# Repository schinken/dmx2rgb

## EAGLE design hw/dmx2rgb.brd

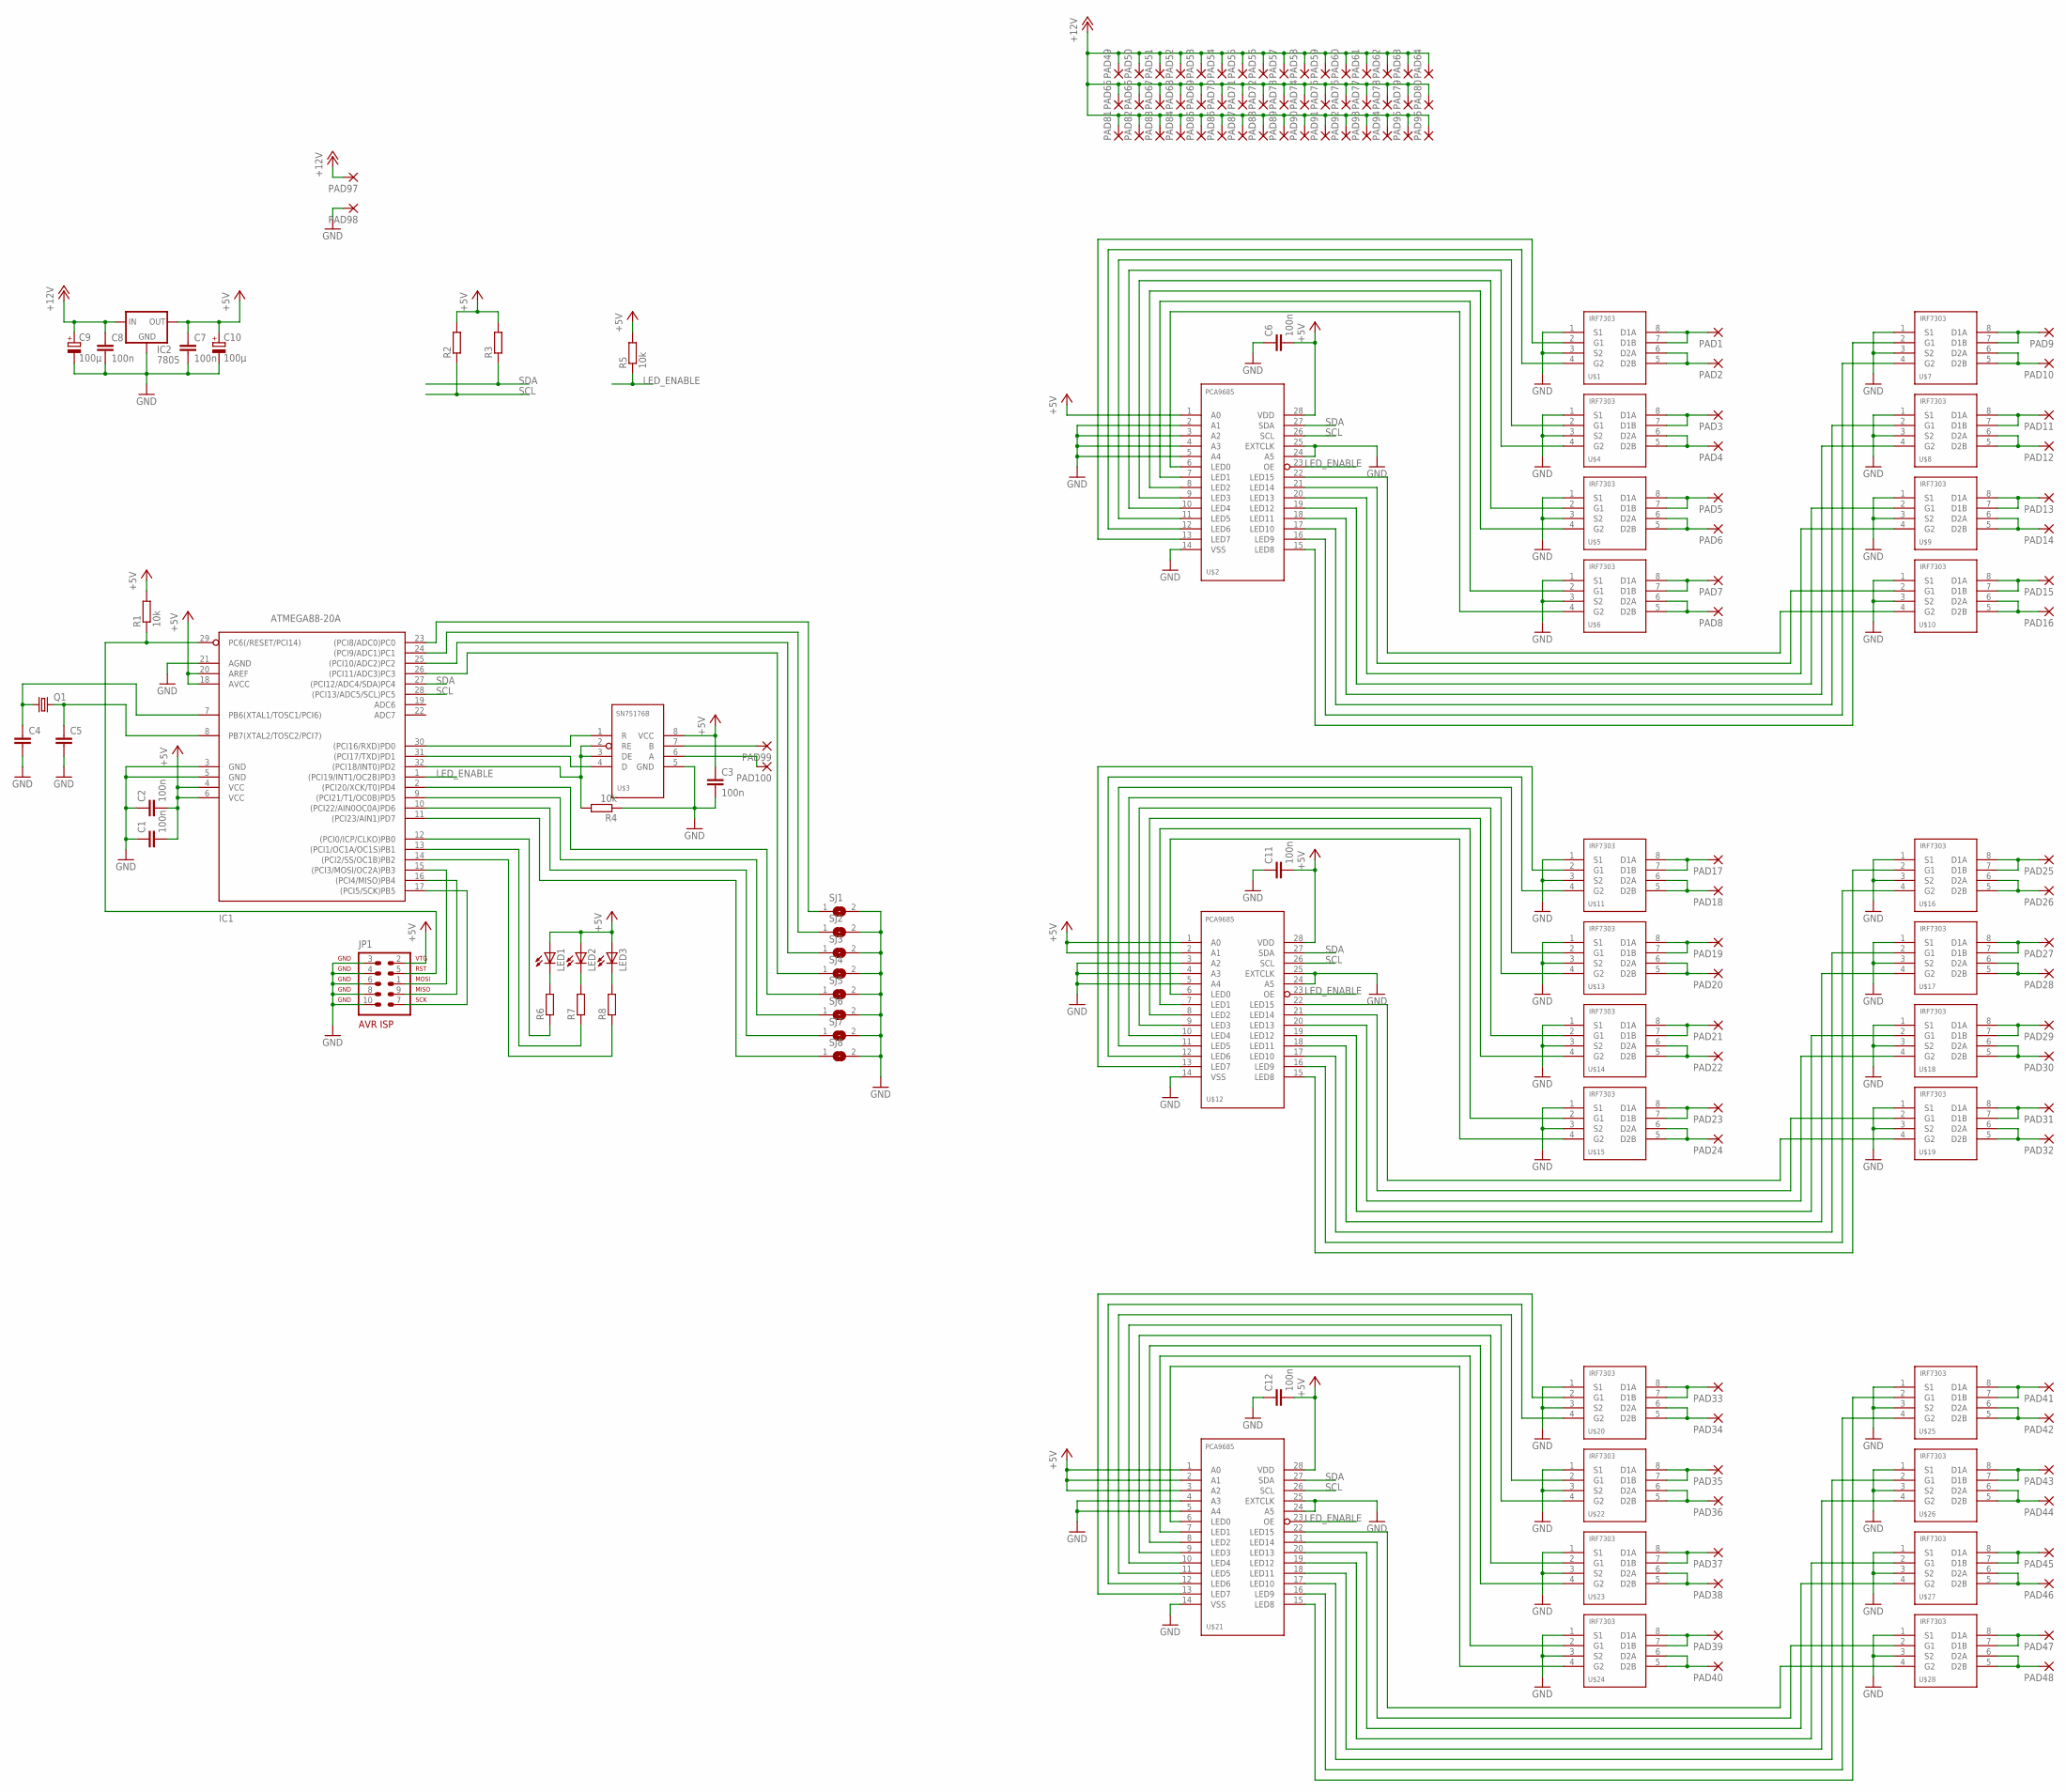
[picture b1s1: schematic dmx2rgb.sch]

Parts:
C1, C2, C3, C6, C7, C8, C11, C12: 100n; CHIP_0805
C4, C5: C0805; CHIP_0805
C9, C10: 100µ; E2,5-7
IC1: ATMEGA88-20A; TQFP32-08
IC2: 7805; 78LXX
JP1: AVR-ISP-10
LED1, LED2, LED3: LEDCHIPLED_0805; CHIPLED_0805
PAD1, PAD2, PAD3, PAD4, PAD5, PAD6, PAD7, PAD8, PAD9, PAD10, PAD11, PAD12, PAD13, PAD14, PAD15, PAD16, PAD17, PAD18, PAD19, PAD20, PAD21, PAD22, PAD23, PAD24, PAD25, PAD26, PAD27, PAD28, PAD29, PAD30, PAD31, PAD32, PAD33, PAD34, PAD35, PAD36, PAD37, PAD38, PAD39, PAD40, PAD41, PAD42, PAD43, PAD44, PAD45, PAD46, PAD47, PAD48, PAD49, PAD50, PAD51, PAD52, PAD53, PAD54, PAD55, PAD56, PAD57, PAD58, PAD59, PAD60, PAD61, PAD62, PAD63, PAD64, PAD65, PAD66, PAD67, PAD68, PAD69, PAD70, PAD71, PAD72, PAD73, PAD74, PAD75, PAD76, PAD77, PAD78, PAD79, PAD80, PAD81, PAD82, PAD83, PAD84, PAD85, PAD86, PAD87, PAD88, PAD89, PAD90, PAD91, PAD92, PAD93, PAD94, PAD95, PAD96, PAD99, PAD100: SMD_PAD_LONG
PAD97, PAD98: SMD5; SMD2,54-5,08
Q1: CRYSTAL49; HC49/S
R1, R4, R5: 10k; CHIP_0805
R2, R3, R6, R7, R8: R0805; CHIP_0805
SJ1, SJ2, SJ3, SJ4, SJ5, SJ6, SJ7, SJ8: SJ
U$1, U$4, U$5, U$6, U$7, U$8, U$9, U$10, U$11, U$13, U$14, U$15, U$16, U$17, U$18, U$19, U$20, U$22, U$23, U$24, U$25, U$26, U$27, U$28: IRF7303; SO8
U$2, U$12, U$21: PCA9685; TSSOP28
U$3: SN75176B; SO8

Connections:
+5V: C1.2, C2.2, C3.1, C6.2, C7.1, C10.+, C11.2, C12.2, IC1.4 (VCC), IC1.6 (VCC), IC1.18 (AVCC), IC1.20 (AREF), IC2.OUT, JP1.2, LED1.A, LED2.A, LED3.A, R1.2, R2.2, R3.2, R5.2, U$2.1 (A0), U$2.28 (VDD), U$3.8 (VCC), U$12.1 (A0), U$12.2 (A1), U$12.28 (VDD), U$21.1 (A0), U$21.2 (A1), U$21.3 (A2), U$21.28 (VDD)
+12V: C8.1, C9.+, IC2.IN, PAD49.P$1, PAD50.P$1, PAD51.P$1, PAD52.P$1, PAD53.P$1, PAD54.P$1, PAD55.P$1, PAD56.P$1, PAD57.P$1, PAD58.P$1, PAD59.P$1, PAD60.P$1, PAD61.P$1, PAD62.P$1, PAD63.P$1, PAD64.P$1, PAD65.P$1, PAD66.P$1, PAD67.P$1, PAD68.P$1, PAD69.P$1, PAD70.P$1, PAD71.P$1, PAD72.P$1, PAD73.P$1, PAD74.P$1, PAD75.P$1, PAD76.P$1, PAD77.P$1, PAD78.P$1, PAD79.P$1, PAD80.P$1, PAD81.P$1, PAD82.P$1, PAD83.P$1, PAD84.P$1, PAD85.P$1, PAD86.P$1, PAD87.P$1, PAD88.P$1, PAD89.P$1, PAD90.P$1, PAD91.P$1, PAD92.P$1, PAD93.P$1, PAD94.P$1, PAD95.P$1, PAD96.P$1, PAD97.1
GND: C1.1, C2.1, C3.2, C4.2, C5.2, C6.1, C7.2, C8.2, C9.-, C10.-, C11.1, C12.1, IC1.3 (GND), IC1.5 (GND), IC1.21 (AGND), IC2.GND, JP1.3, JP1.4, JP1.6, JP1.8, JP1.10, PAD98.1, R4.1, SJ1.2, SJ2.2, SJ3.2, SJ4.2, SJ5.2, SJ6.2, SJ7.2, SJ8.2, U$1.1 (S1), U$1.3 (S2), U$2.2 (A1), U$2.3 (A2), U$2.4 (A3), U$2.5 (A4), U$2.14 (VSS), U$2.24 (A5), U$2.25 (EXTCLK), U$3.5 (GND), U$4.1 (S1), U$4.3 (S2), U$5.1 (S1), U$5.3 (S2), U$6.1 (S1), U$6.3 (S2), U$7.1 (S1), U$7.3 (S2), U$8.1 (S1), U$8.3 (S2), U$9.1 (S1), U$9.3 (S2), U$10.1 (S1), U$10.3 (S2), U$11.1 (S1), U$11.3 (S2), U$12.3 (A2), U$12.4 (A3), U$12.5 (A4), U$12.14 (VSS), U$12.24 (A5), U$12.25 (EXTCLK), U$13.1 (S1), U$13.3 (S2), U$14.1 (S1), U$14.3 (S2), U$15.1 (S1), U$15.3 (S2), U$16.1 (S1), U$16.3 (S2), U$17.1 (S1), U$17.3 (S2), U$18.1 (S1), U$18.3 (S2), U$19.1 (S1), U$19.3 (S2), U$20.1 (S1), U$20.3 (S2), U$21.4 (A3), U$21.5 (A4), U$21.14 (VSS), U$21.24 (A5), U$21.25 (EXTCLK), U$22.1 (S1), U$22.3 (S2), U$23.1 (S1), U$23.3 (S2), U$24.1 (S1), U$24.3 (S2), U$25.1 (S1), U$25.3 (S2), U$26.1 (S1), U$26.3 (S2), U$27.1 (S1), U$27.3 (S2), U$28.1 (S1), U$28.3 (S2)
LED_ENABLE: IC1.1 ((PCI19/INT1/OC2B)PD3), R5.1, U$2.23 (OE), U$12.23 (OE), U$21.23 (OE)
unnamed: IC1.30 ((PCI16/RXD)PD0), U$3.1 (R)
unnamed: IC1.31 ((PCI17/TXD)PD1), U$3.4 (D)
unnamed: LED3.C, R8.2
unnamed: IC1.32 ((PCI18/INT0)PD2), R4.2, U$3.2 (RE), U$3.3 (DE)
unnamed: PAD1.P$1, U$1.7 (D1B), U$1.8 (D1A)
unnamed: PAD2.P$1, U$1.5 (D2B), U$1.6 (D2A)
unnamed: IC1.29 (PC6(/RESET/PCI14)), JP1.5, R1.1
unnamed: IC1.15 ((PCI3/MOSI/OC2A)PB3), JP1.1
unnamed: IC1.16 ((PCI4/MISO)PB4), JP1.9
unnamed: IC1.17 ((PCI5/SCK)PB5), JP1.7
unnamed: PAD99.P$1, U$3.7 (B)
unnamed: PAD3.P$1, U$4.7 (D1B), U$4.8 (D1A)
unnamed: PAD4.P$1, U$4.5 (D2B), U$4.6 (D2A)
unnamed: LED2.C, R7.2
unnamed: U$2.10 (LED4), U$4.4 (G2)
unnamed: PAD5.P$1, U$5.7 (D1B), U$5.8 (D1A)
unnamed: PAD6.P$1, U$5.5 (D2B), U$5.6 (D2A)
unnamed: U$2.9 (LED3), U$5.2 (G1)
unnamed: U$2.8 (LED2), U$5.4 (G2)
unnamed: PAD7.P$1, U$6.7 (D1B), U$6.8 (D1A)
unnamed: PAD8.P$1, U$6.5 (D2B), U$6.6 (D2A)
unnamed: U$2.7 (LED1), U$6.2 (G1)
unnamed: U$2.6 (LED0), U$6.4 (G2)
unnamed: PAD9.P$1, U$7.7 (D1B), U$7.8 (D1A)
unnamed: PAD10.P$1, U$7.5 (D2B), U$7.6 (D2A)
unnamed: LED1.C, R6.2
unnamed: IC1.12 ((PCI0/ICP/CLKO)PB0), R6.1
unnamed: PAD11.P$1, U$8.7 (D1B), U$8.8 (D1A)
unnamed: PAD12.P$1, U$8.5 (D2B), U$8.6 (D2A)
unnamed: IC1.13 ((PCI1/OC1A/OC1S)PB1), R7.1
unnamed: IC1.14 ((PCI2/SS/OC1B)PB2), R8.1
unnamed: PAD13.P$1, U$9.7 (D1B), U$9.8 (D1A)
unnamed: PAD14.P$1, U$9.5 (D2B), U$9.6 (D2A)
unnamed: IC1.26 ((PCI11/ADC3)PC3), SJ4.1
unnamed: IC1.25 ((PCI10/ADC2)PC2), SJ3.1
unnamed: PAD15.P$1, U$10.7 (D1B), U$10.8 (D1A)
unnamed: PAD16.P$1, U$10.5 (D2B), U$10.6 (D2A)
unnamed: IC1.24 ((PCI9/ADC1)PC1), SJ2.1
unnamed: IC1.23 ((PCI8/ADC0)PC0), SJ1.1
unnamed: C4.1, IC1.7 (PB6(XTAL1/TOSC1/PCI6)), Q1.1
unnamed: C5.1, IC1.8 (PB7(XTAL2/TOSC2/PCI7)), Q1.2
unnamed: IC1.2 ((PCI20/XCK/T0)PD4), SJ5.1
unnamed: IC1.9 ((PCI21/T1/OC0B)PD5), SJ6.1
unnamed: IC1.10 ((PCI22/AIN0OC0A)PD6), SJ7.1
unnamed: IC1.11 ((PCI23/AIN1)PD7), SJ8.1
unnamed: PAD100.P$1, U$3.6 (A)
unnamed: PAD17.P$1, U$11.7 (D1B), U$11.8 (D1A)
unnamed: PAD18.P$1, U$11.5 (D2B), U$11.6 (D2A)
unnamed: U$1.2 (G1), U$2.13 (LED7)
unnamed: U$1.4 (G2), U$2.12 (LED6)
unnamed: U$2.11 (LED5), U$4.2 (G1)
unnamed: U$2.15 (LED8), U$7.2 (G1)
unnamed: U$2.16 (LED9), U$7.4 (G2)
unnamed: U$2.17 (LED10), U$8.2 (G1)
unnamed: U$2.18 (LED11), U$8.4 (G2)
unnamed: U$2.19 (LED12), U$9.2 (G1)
unnamed: U$2.20 (LED13), U$9.4 (G2)
unnamed: U$2.21 (LED14), U$10.2 (G1)
unnamed: U$2.22 (LED15), U$10.4 (G2)
unnamed: PAD19.P$1, U$13.7 (D1B), U$13.8 (D1A)
unnamed: PAD20.P$1, U$13.5 (D2B), U$13.6 (D2A)
unnamed: U$12.10 (LED4), U$13.4 (G2)
unnamed: PAD21.P$1, U$14.7 (D1B), U$14.8 (D1A)
unnamed: PAD22.P$1, U$14.5 (D2B), U$14.6 (D2A)
unnamed: U$12.9 (LED3), U$14.2 (G1)
unnamed: U$12.8 (LED2), U$14.4 (G2)
unnamed: PAD23.P$1, U$15.7 (D1B), U$15.8 (D1A)
unnamed: PAD24.P$1, U$15.5 (D2B), U$15.6 (D2A)
unnamed: U$12.7 (LED1), U$15.2 (G1)
unnamed: U$12.6 (LED0), U$15.4 (G2)
unnamed: PAD25.P$1, U$16.7 (D1B), U$16.8 (D1A)
unnamed: PAD26.P$1, U$16.5 (D2B), U$16.6 (D2A)
unnamed: PAD27.P$1, U$17.7 (D1B), U$17.8 (D1A)
unnamed: PAD28.P$1, U$17.5 (D2B), U$17.6 (D2A)
unnamed: PAD29.P$1, U$18.7 (D1B), U$18.8 (D1A)
unnamed: PAD30.P$1, U$18.5 (D2B), U$18.6 (D2A)
unnamed: PAD31.P$1, U$19.7 (D1B), U$19.8 (D1A)
unnamed: PAD32.P$1, U$19.5 (D2B), U$19.6 (D2A)
unnamed: U$11.2 (G1), U$12.13 (LED7)
unnamed: U$11.4 (G2), U$12.12 (LED6)
unnamed: U$12.11 (LED5), U$13.2 (G1)
unnamed: U$12.15 (LED8), U$16.2 (G1)
unnamed: U$12.16 (LED9), U$16.4 (G2)
unnamed: U$12.17 (LED10), U$17.2 (G1)
unnamed: U$12.18 (LED11), U$17.4 (G2)
unnamed: U$12.19 (LED12), U$18.2 (G1)
unnamed: U$12.20 (LED13), U$18.4 (G2)
unnamed: U$12.21 (LED14), U$19.2 (G1)
unnamed: U$12.22 (LED15), U$19.4 (G2)
unnamed: PAD33.P$1, U$20.7 (D1B), U$20.8 (D1A)
unnamed: PAD34.P$1, U$20.5 (D2B), U$20.6 (D2A)
unnamed: PAD35.P$1, U$22.7 (D1B), U$22.8 (D1A)
unnamed: PAD36.P$1, U$22.5 (D2B), U$22.6 (D2A)
unnamed: U$21.10 (LED4), U$22.4 (G2)
unnamed: PAD37.P$1, U$23.7 (D1B), U$23.8 (D1A)
unnamed: PAD38.P$1, U$23.5 (D2B), U$23.6 (D2A)
unnamed: U$21.9 (LED3), U$23.2 (G1)
unnamed: U$21.8 (LED2), U$23.4 (G2)
unnamed: PAD39.P$1, U$24.7 (D1B), U$24.8 (D1A)
unnamed: PAD40.P$1, U$24.5 (D2B), U$24.6 (D2A)
unnamed: U$21.7 (LED1), U$24.2 (G1)
unnamed: U$21.6 (LED0), U$24.4 (G2)
unnamed: PAD41.P$1, U$25.7 (D1B), U$25.8 (D1A)
unnamed: PAD42.P$1, U$25.5 (D2B), U$25.6 (D2A)
unnamed: PAD43.P$1, U$26.7 (D1B), U$26.8 (D1A)
unnamed: PAD44.P$1, U$26.5 (D2B), U$26.6 (D2A)
unnamed: PAD45.P$1, U$27.7 (D1B), U$27.8 (D1A)
unnamed: PAD46.P$1, U$27.5 (D2B), U$27.6 (D2A)
unnamed: PAD47.P$1, U$28.7 (D1B), U$28.8 (D1A)
unnamed: PAD48.P$1, U$28.5 (D2B), U$28.6 (D2A)
unnamed: U$20.2 (G1), U$21.13 (LED7)
unnamed: U$20.4 (G2), U$21.12 (LED6)
unnamed: U$21.11 (LED5), U$22.2 (G1)
unnamed: U$21.15 (LED8), U$25.2 (G1)
unnamed: U$21.16 (LED9), U$25.4 (G2)
unnamed: U$21.17 (LED10), U$26.2 (G1)
unnamed: U$21.18 (LED11), U$26.4 (G2)
unnamed: U$21.19 (LED12), U$27.2 (G1)
unnamed: U$21.20 (LED13), U$27.4 (G2)
unnamed: U$21.21 (LED14), U$28.2 (G1)
unnamed: U$21.22 (LED15), U$28.4 (G2)
SCL: IC1.28 ((PCI13/ADC5/SCL)PC5), R2.1, U$2.26 (SCL), U$12.26 (SCL), U$21.26 (SCL)
SDA: IC1.27 ((PCI12/ADC4/SDA)PC4), R3.1, U$2.27 (SDA), U$12.27 (SDA), U$21.27 (SDA)

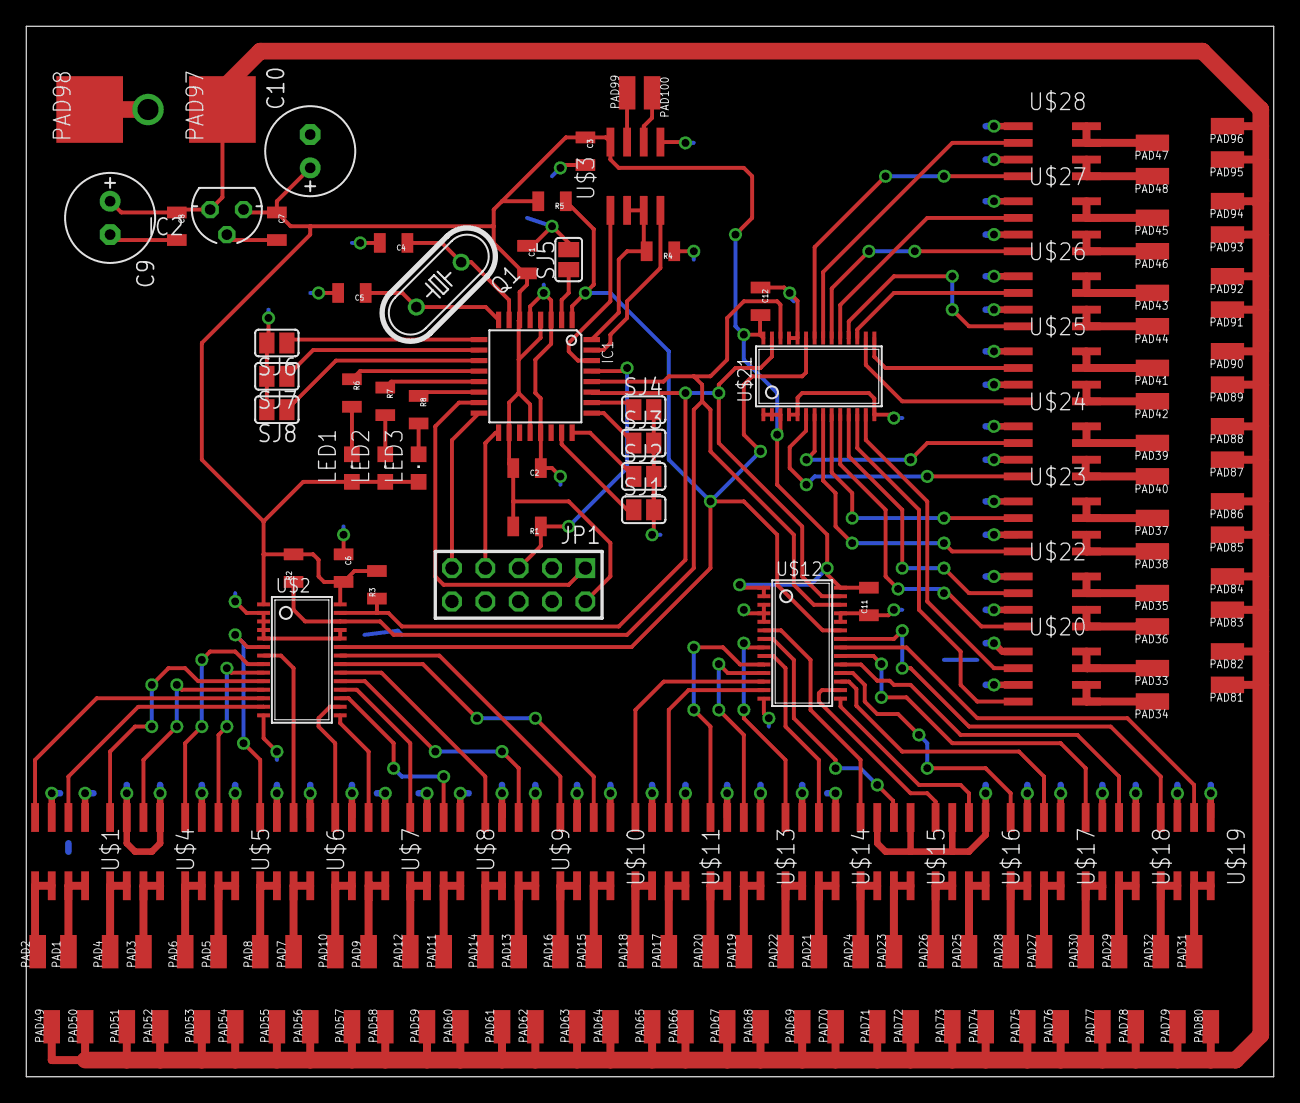
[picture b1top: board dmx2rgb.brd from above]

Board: 2 copper layers, 95.0 x 80.0 mm, 163 parts (0 on the bottom side), 127 nets.

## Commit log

2012-08-23 datasheets parts
2012-08-23 eagle project initial part library
2012-08-23 added pwm driver and fet devices added some other devices as well typo fix
2012-08-27 basic schematics added new parts to library
2012-08-27 added some pull ups added layout file
2012-08-27 adressing through solder jumpers
2012-09-11 all parts added some parts placed
2012-09-13 pcb finished prepared for 0.3mm milling
2012-09-14 removed drilling below mcu
2012-10-02 optimized and doublesided
2012-10-02 deleted private file
2012-10-10 Added gitignore
2012-10-10 removed uneccesary files
2012-10-10 changed dmx buffer check
2012-10-10 dmx reading approach
2012-10-10 working dmx rx
2012-10-10 Removed back/front buffering
2012-10-11 added pca9685 prototype
2012-10-11 fixed syntax errors
2012-10-11 Added experimental baudrate
2012-10-11 moving ciel12 to progmem
2012-10-11 read correct amount of data
2012-10-11 added mapping, using dmx values for pwm
2012-10-11 PCA9685 abstraction
2012-10-11 Added i2c and pca c file
2012-10-11 Added configuration file
2012-10-11 Added i2c library
2012-10-11 added git ignore
2012-10-11 enabled other pwm chips
2012-10-11 set correct channel num
2012-10-11 set i2c freq to 400khz
2012-10-11 removed file
2012-10-12 Added led toggle
2012-10-23 Changed dmx channel, code cleanup
2012-11-04 Reverted changes
2012-11-04 merge
2012-11-06 fixed indention
2012-11-06 pwm frequency added, disaligns the 3 PCA chip clock, prevents flickering
2013-02-10 applied consistend code style
2013-02-12 added direct serial mode
2013-02-12 only read data needed (48 bytes)
2013-02-12 changed baudrate to 230400, using util/setbaud
2013-02-12 code cleanup
2013-02-17 use only 1 stopbit
2013-02-17 init array, changed bit rate
2013-02-17 fixed loop (c99 mode)
2013-02-18 changed baudrate
2015-08-29 Remove inline statement
2015-08-29 Add fuses
2015-08-29 Remove unused variable
